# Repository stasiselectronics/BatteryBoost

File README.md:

# BatteryBoost Documentation site

This branch contains all the source files used to build the documentation website hosted here on Github pages. The site uses the jekyll theme [Minimal Mistakes](https://mmistakes.github.io/minimal-mistakes/about/) from [Michael Rose](https://mademistakes.com/).

Here you can view more details about the design, with some technical explanations.

## Troubleshooting

If you have a question about using Jekyll, start a discussion on the [Jekyll Forum](https://talk.jekyllrb.com/) or [StackOverflow](https://stackoverflow.com/questions/tagged/jekyll). Other resources:

- [Ruby 101](https://jekyllrb.com/docs/ruby-101/)
- [Setting up a Jekyll site with GitHub Pages](https://jekyllrb.com/docs/github-pages/)
- [Configuring GitHub Metadata](https://github.com/jekyll/github-metadata/blob/master/docs/configuration.md#configuration) to work properly when developing locally and avoid `No GitHub API authentication could be found. Some fields may be missing or have incorrect data.` warnings.

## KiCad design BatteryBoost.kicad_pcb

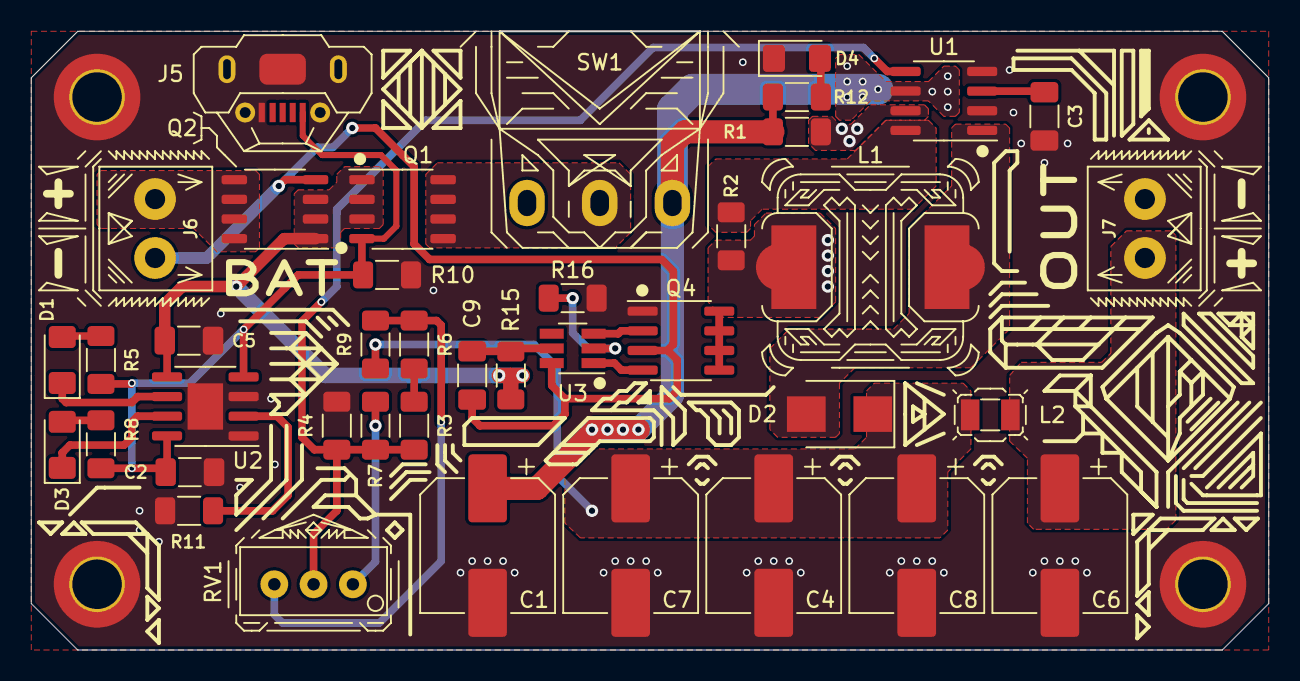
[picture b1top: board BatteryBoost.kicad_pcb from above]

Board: 2 copper layers, 80.0 x 40.0 mm, 44 parts (0 on the bottom side), 28 nets.

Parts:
C1, C4, C6, C7: 100uF ±20% 50V; CP_Elec_8x10.5
C2, C5: 10uF ±10% 25V X5R; C_1206_3216Metric_Pad1.33x1.80mm_HandSolder
C3: 1.5nF ±10% 50V X7R 1206; C_1206_3216Metric_Pad1.33x1.80mm_HandSolder
C8: 100uF ±20% 50V (x3); CP_Elec_8x10.5
C9: 100nF ±10% 50V X7R; C_1206_3216Metric_Pad1.33x1.80mm_HandSolder
D1, D4: Blue LED; D_1206_3216Metric_Pad1.42x1.75mm_HandSolder
D2: 40V 3A 500mV@3A; D_SMB
D3: Red LED; D_1206_3216Metric_Pad1.42x1.75mm_HandSolder
J1, J2, J3, J4: Mounting Hole; MountingHole_3.2mm_M3_DIN965_Pad_TopBottom
J5: USB_B_Micro; U-F-M5DD-Y-L
J6: Battery; WJ124-3.81-2P
J7: Output; WJ124-3.81-2P
L1: 150uH ±20% 2.15A 280mΩ; Inductor_SLH_12x12x8_HandSolder
L2: 1uH ±20% 3.29A 59mΩ; L_2.5x2.0_Hand_Solder
Q1: -40V 7.5A 2.5V @ 250uA 40mΩ @ 6A; SOP-8_3.9x4.9mm_P1.27mm
Q2: -40V 7.5A 40mΩ @ 6A; SOP-8_3.9x4.9mm_P1.27mm
Q4: 20V 7.5A 24mΩ @ 2.5Vgs; SOIC-8_3.9x4.9mm_P1.27mm
R1: 0.3R; R_1206_3216Metric_Pad1.30x1.75mm_HandSolder
R2: 180R; R_1206_3216Metric_Pad1.30x1.75mm_HandSolder
R3: 499k 0.25W 1%; R_1206_3216Metric_Pad1.30x1.75mm_HandSolder
R4: 16k; R_1206_3216Metric_Pad1.30x1.75mm_HandSolder
R5, R8, R10, R12: 10k; R_1206_3216Metric_Pad1.30x1.75mm_HandSolder
R6: 9.1k 1% 0.25W; R_1206_3216Metric_Pad1.30x1.75mm_HandSolder
R7: 0R; R_1206_3216Metric_Pad1.30x1.75mm_HandSolder
R9: 47.5kΩ ±1% 0.25W; R_1206_3216Metric_Pad1.30x1.75mm_HandSolder
R11, R16: 1.2kΩ ±1% 0.25W; R_1206_3216Metric_Pad1.30x1.75mm_HandSolder
R15: 330R ±1% 0.25W; R_1206_3216Metric_Pad1.30x1.75mm_HandSolder
RV1: Variable Resistors 500kΩ ±10%; Potentiometer_3296W-1-504
SW1: SW_SPDT; Switch_SS-12D06L5
U1: SP34063AEN; SOIC-8_3.9x4.9mm_P1.27mm
U2: TP4056; SOIC-8-1EP_3.9x4.9mm_P1.27mm_EP2.29x3mm
U3: AP9101CK6; SOT-23-6_Handsoldering

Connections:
+5V: C2.1, J5.1, Q1.G, R5.2, R8.1, R10.2, U2.4, U2.8
/Raw_Batt_+: J6.1, Q2.D
/Raw_Batt_-: C9.2, J6.2, Q2.G, Q4.3, U3.6
/Vout: C6.1, J7.1, L2.2
GND: C1.2, C2.2, C3.2, C4.2, C5.2, C6.2, C7.2, C8.2, D4.1, J1.1, J2.1, J3.1, J4.1, J5.5, J5.6, J7.2, Q4.1, R4.1, R10.1, R11.2, R16.2, U1.2, U1.4, U2.1, U2.3, U2.9
unnamed: C3.1, U1.3
unnamed: C9.1, R15.2, U3.5
unnamed: D1.1, U2.6
unnamed: D1.2, R5.1
unnamed: D2.2, L1.1, U1.1
unnamed: D3.1, U2.7
unnamed: D3.2, R8.2
unnamed: D4.2, R12.2
unnamed: L1.2, R1.1, R2.2, U1.7
unnamed: Q1.D, SW1.2
unnamed: Q4.2, U3.3
unnamed: Q4.4, U3.1
unnamed: Q4.5, Q4.6, Q4.7, Q4.8
unnamed: R2.1, U1.8
unnamed: R3.2, R6.1
unnamed: R6.2, R9.1, RV1.1
unnamed: R7.1, RV1.3
unnamed: R11.1, U2.2
unnamed: R16.1, U3.2
SMPS_Output: C4.1, C7.1, C8.1, D2.1, L2.1, R9.2
SMPS_Pwr: C1.1, R1.2, R12.1, SW1.3, U1.6
SMPS_VoltageSetting: R3.1, R4.2, R7.2, RV1.2, U1.5
VBATT: C5.1, Q1.S, Q2.S, R15.1, U2.5

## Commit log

2021-05-14 add files from fume extractor project
2021-05-14 change project name
2021-05-14 update schematic and layout
2021-05-14 add chamfer to board edge
2021-05-15 finalize designs
2021-05-15 Finalize schematic and layout
2021-05-16 Update layout and add art files
2021-05-16 A01 Release Files
2021-05-16 Rename Fabrication Release Archive
2021-05-20 update drawing
2021-05-20 add missing library table
2021-05-20 add render images from KiCAD
2021-06-08 Add missing symbol library reference
2021-06-08 change D2 to Schottky Barrier Diode for faster recovery time
2021-06-08 Change source select method to diode array
2021-06-08 update power inductor to 2.15 A version
2021-06-09 Add Schematic for revision A01
2021-06-09 Re-arrange schematic
2021-06-09 Update schematic revision to A02
2021-06-09 Change source selection method
2021-06-09 Clear board
2021-06-09 update board size to 80x40mm
2021-06-09 update component part info
2021-06-10 Start placing footprints on board
2021-06-10 Add PMOS footprint and symbol
2021-06-16 Add AP910 Symbol
2021-06-17 Add battery protection circuit
2021-06-17 Preliminary placement for protection circuit
2021-06-18 remove BJT power indication
2021-06-18 remove BJT circuit layout
2021-06-21 add a3 size page template
2021-06-21 Change schematic to A3 size
2021-06-21 Update net names
2021-06-21 Add footprint for filter inductor
2021-06-21 Add new filter inductor footprint
2021-06-21 place and route battery protection circuit
2021-06-21 move potentiometer
2021-06-22 Add artwork and finalize layout
2021-06-27 Fix 9.1k Resistor order code
2021-06-27 update exported SVG
2021-06-27 Update routing
2021-06-27 Update bottom artwork
2021-06-27 finalize bottom artwork
2021-06-27 Add A02 Fabrication Files
2021-06-27 Update fabrication files
2021-06-27 Update part info for sourcing issues
2021-06-29 Add A02 Schematic
2021-07-01 remove fp-info-cache
2021-07-13 add test procedure page
2021-07-13 update content
2021-07-23 add bill of materials for A02
2021-07-24 add A02 image
2021-07-26 Update Bill of Materials
2021-08-11 add some test reporting
2021-08-15 add index
2021-08-15 Add template from Gitbook
2021-08-15 add Gemfile
2021-08-15 add gh-pages dependancy
2021-08-15 update url in config
2021-08-15 update gemfile
2021-08-15 update baseurl
2021-08-15 add page
2021-08-15 Add content from MicroBBPS to use as a template
2021-08-15 remove MicroBBPS pictures
2021-08-15 Add photos
2021-08-15 update config
2021-08-18 add BOM as pdf
2021-08-22 remove extra files
2021-11-15 Add FreeCAD files
2021-11-15 update enclosure files
2021-11-16 fix clearance for main switch and update STLs
